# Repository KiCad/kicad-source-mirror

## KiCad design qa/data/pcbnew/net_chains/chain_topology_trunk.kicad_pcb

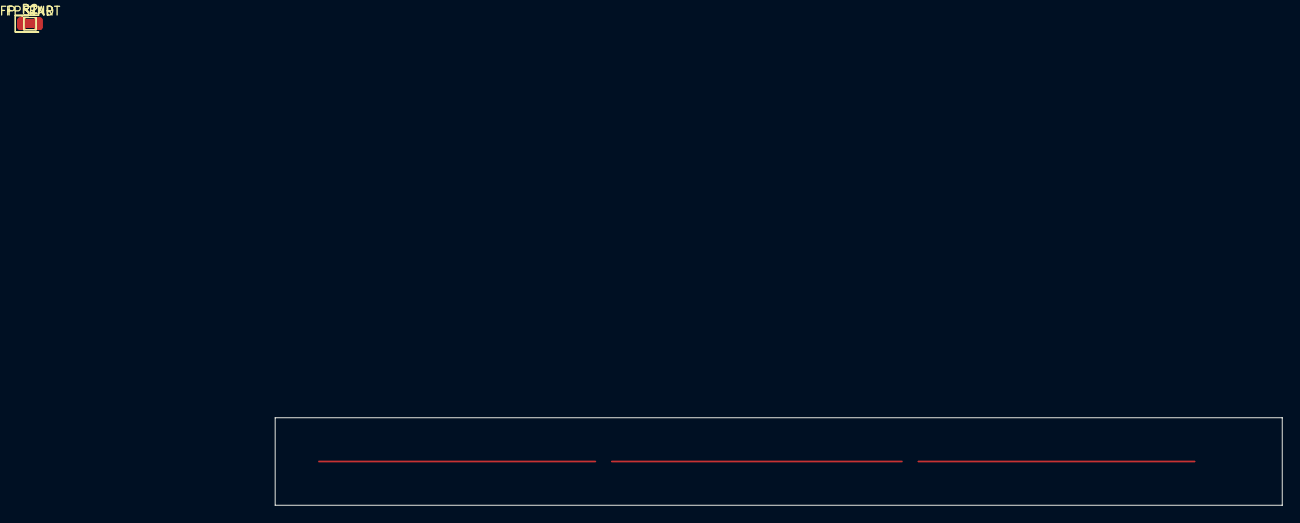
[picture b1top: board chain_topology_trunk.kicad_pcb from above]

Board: 2 copper layers, 115.0 x 10.0 mm, 4 parts (0 on the bottom side), 3 nets.

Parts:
FP_END: TestPoint_Pad_1.0x1.0mm
FP_START: TestPoint_Pad_1.0x1.0mm
R1, R2: LED_0805_2012Metric

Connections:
/NET_A: FP_START.1, R1.1
/NET_B: R1.2, R2.1
/NET_C: FP_END.1, R2.2

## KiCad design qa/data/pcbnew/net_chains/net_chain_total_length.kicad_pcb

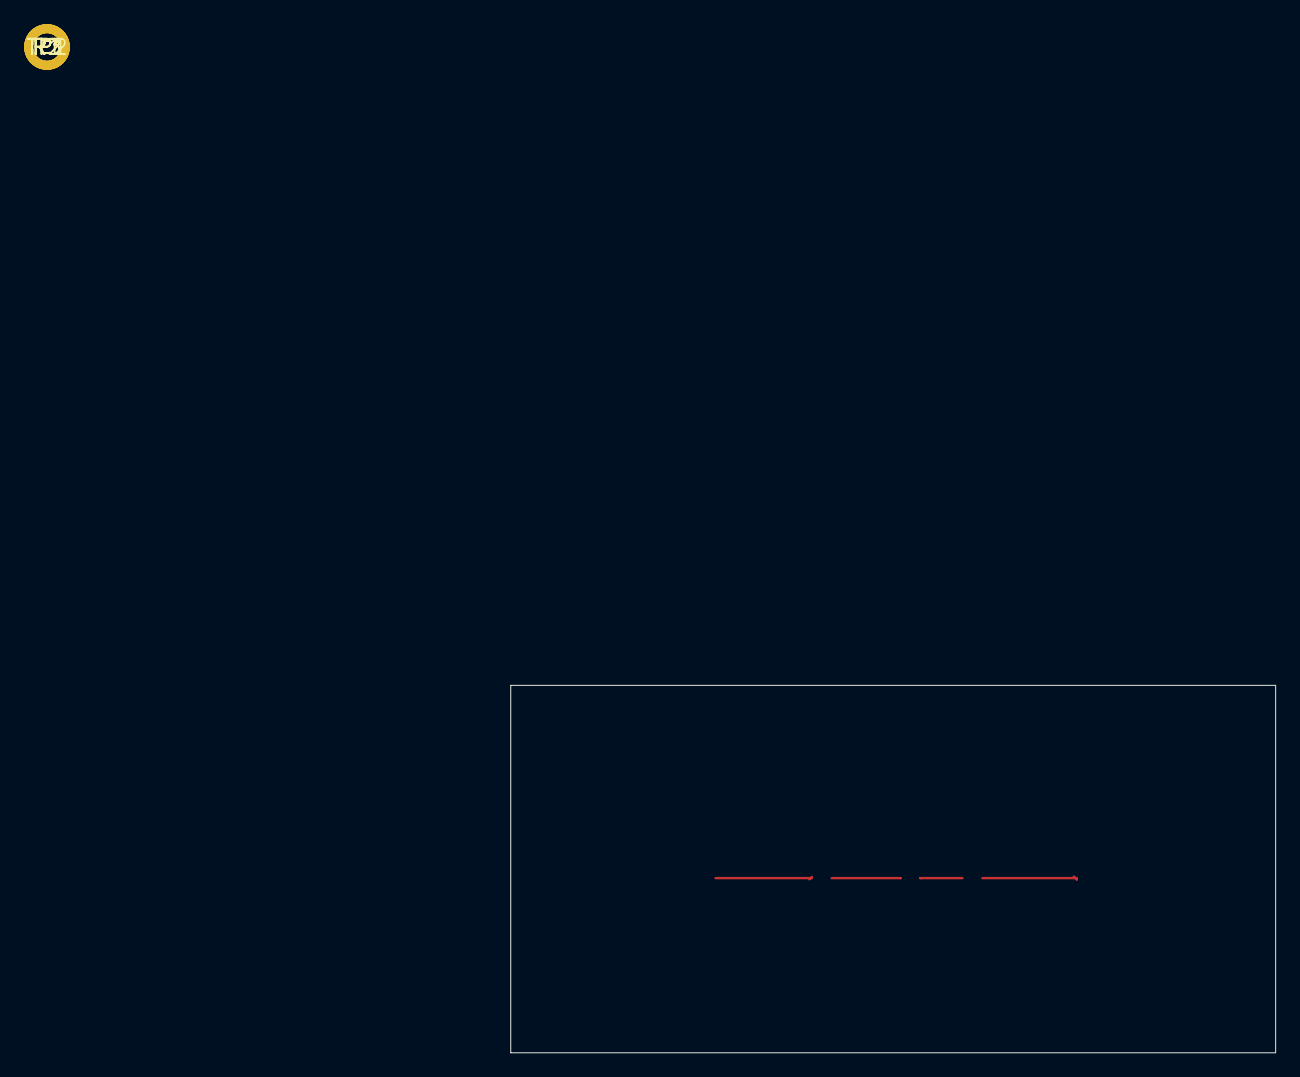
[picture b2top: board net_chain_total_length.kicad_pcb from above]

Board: 2 copper layers, 63.5 x 30.5 mm, 5 parts (0 on the bottom side), 4 nets.

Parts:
R1, R2, R3: R_0603_1608Metric
TP1, TP2: MountingHole_2.2mm_M2_DIN965_Pad

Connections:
unnamed: R1.1, TP2.1
unnamed: R1.2, R2.1
unnamed: R2.2, R3.1
unnamed: R3.2, TP1.1
